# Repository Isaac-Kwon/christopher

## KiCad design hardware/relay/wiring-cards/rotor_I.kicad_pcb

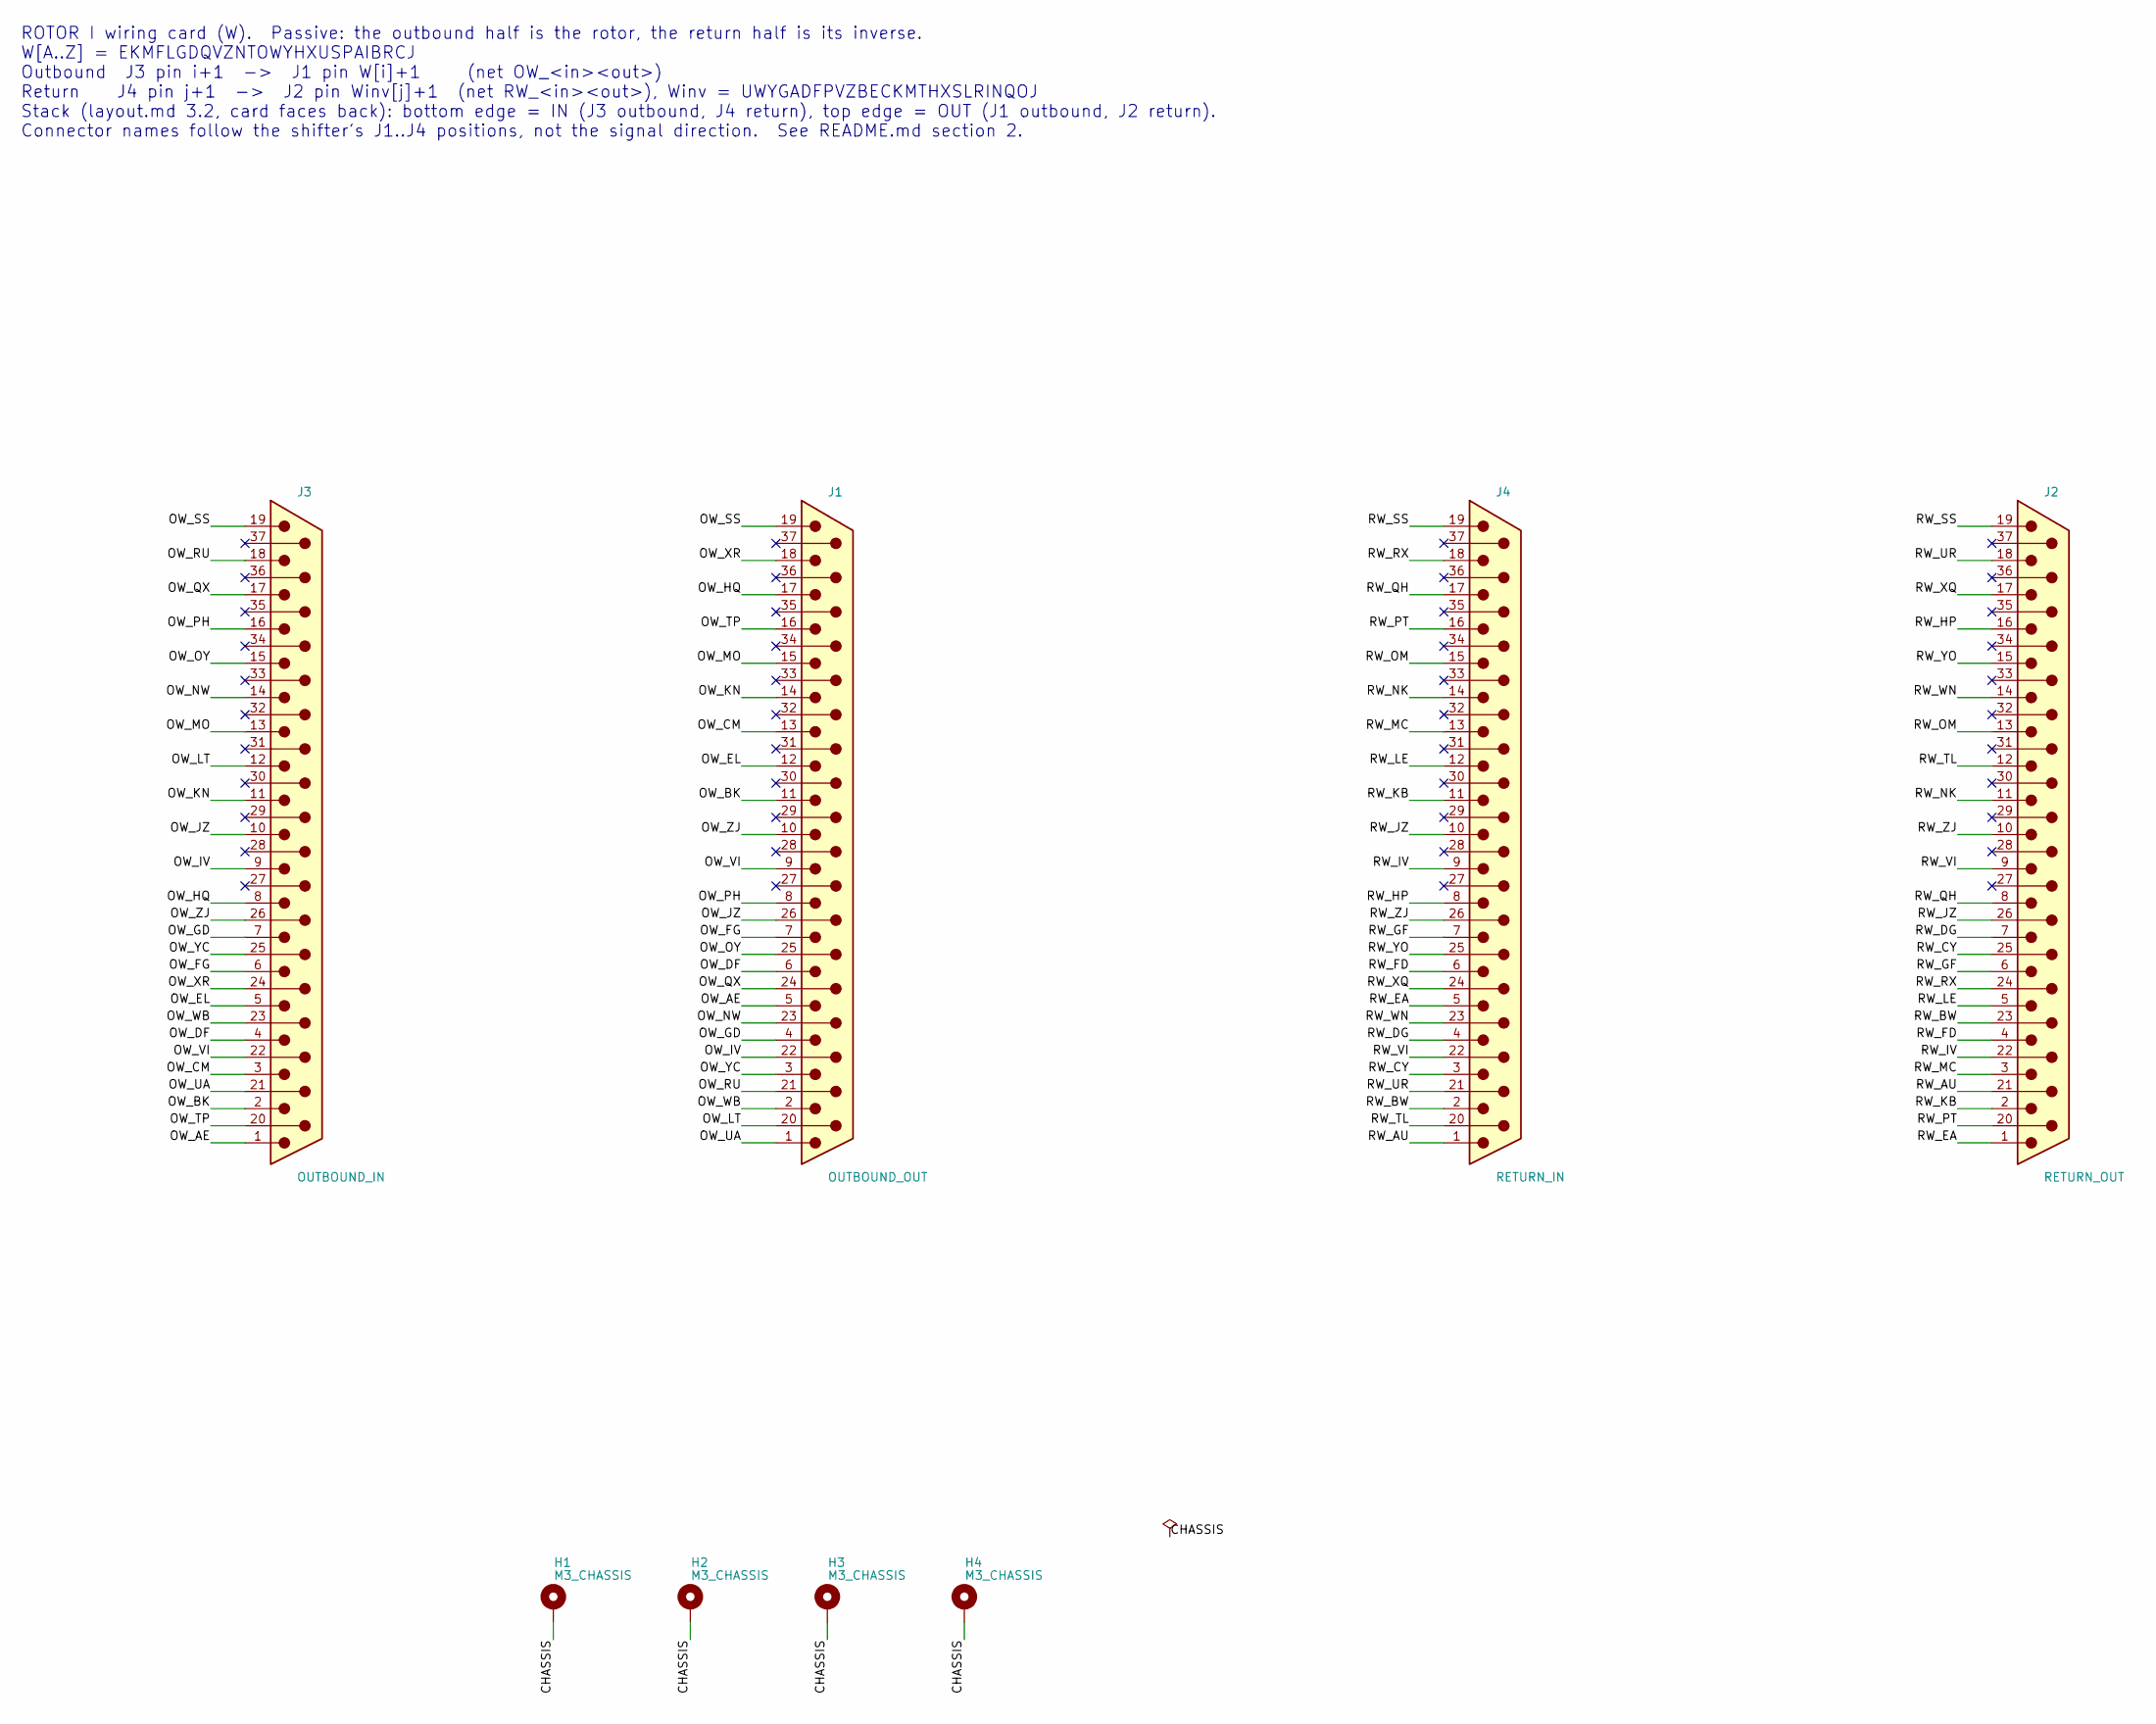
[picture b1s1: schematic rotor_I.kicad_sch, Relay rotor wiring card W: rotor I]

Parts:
H1, H2, H3, H4: M3_CHASSIS; MountingHole_3.2mm_M3_Pad
J1: OUTBOUND_OUT; DSUB-37_Pins_Horizontal_P2.77x2.84mm_EdgePinOffset9.90mm_Ho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
J2: RETURN_OUT; DSUB-37_Pins_Horizontal_P2.77x2.84mm_EdgePinOffset9.90mm_Ho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
J3: OUTBOUND_IN; DSUB-37_Pins_Horizontal_P2.77x2.84mm_EdgePinOffset9.90mm_Ho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
J4: RETURN_IN; DSUB-37_Pins_Horizontal_P2.77x2.84mm_EdgePinOffset9.90mm_Ho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

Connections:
/CHASSIS: H1.1, H2.1, H3.1, H4.1, J1.SH, J2.SH, J3.SH, J4.SH
/OW_AE: J1.5, J3.1
/OW_BK: J1.11, J3.2
/OW_CM: J1.13, J3.3
/OW_DF: J1.6, J3.4
/OW_EL: J1.12, J3.5
/OW_FG: J1.7, J3.6
/OW_GD: J1.4, J3.7
/OW_HQ: J1.17, J3.8
/OW_IV: J1.22, J3.9
/OW_JZ: J1.26, J3.10
/OW_KN: J1.14, J3.11
/OW_LT: J1.20, J3.12
/OW_MO: J1.15, J3.13
/OW_NW: J1.23, J3.14
/OW_OY: J1.25, J3.15
/OW_PH: J1.8, J3.16
/OW_QX: J1.24, J3.17
/OW_RU: J1.21, J3.18
/OW_SS: J1.19, J3.19
/OW_TP: J1.16, J3.20
/OW_UA: J1.1, J3.21
/OW_VI: J1.9, J3.22
/OW_WB: J1.2, J3.23
/OW_XR: J1.18, J3.24
/OW_YC: J1.3, J3.25
/OW_ZJ: J1.10, J3.26
/RW_AU: J2.21, J4.1
/RW_BW: J2.23, J4.2
/RW_CY: J2.25, J4.3
/RW_DG: J2.7, J4.4
/RW_EA: J2.1, J4.5
/RW_FD: J2.4, J4.6
/RW_GF: J2.6, J4.7
/RW_HP: J2.16, J4.8
/RW_IV: J2.22, J4.9
/RW_JZ: J2.26, J4.10
/RW_KB: J2.2, J4.11
/RW_LE: J2.5, J4.12
/RW_MC: J2.3, J4.13
/RW_NK: J2.11, J4.14
/RW_OM: J2.13, J4.15
/RW_PT: J2.20, J4.16
/RW_QH: J2.8, J4.17
/RW_RX: J2.24, J4.18
/RW_SS: J2.19, J4.19
/RW_TL: J2.12, J4.20
/RW_UR: J2.18, J4.21
/RW_VI: J2.9, J4.22
/RW_WN: J2.14, J4.23
/RW_XQ: J2.17, J4.24
/RW_YO: J2.15, J4.25
/RW_ZJ: J2.10, J4.26

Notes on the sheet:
ROTOR I wiring card (W). Passive: the outbound half is the rotor, the return half is its inverse. W[A..Z] = EKMFLGDQVZNTOWYHXUSPAIBRCJ Outbound J3 pin i+1 -> J1 pin W[i]+1 (net OW_<in><out>) Return J4 pin j+1 -> J2 pin Winv[j]+1 (net RW_<in><out>), Winv = UWYGADFPVZBECKMTHXSLRINQOJ Stack (layout.md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

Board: 2 copper layers, 8 parts (0 on the bottom side), 53 nets, no tracks yet.

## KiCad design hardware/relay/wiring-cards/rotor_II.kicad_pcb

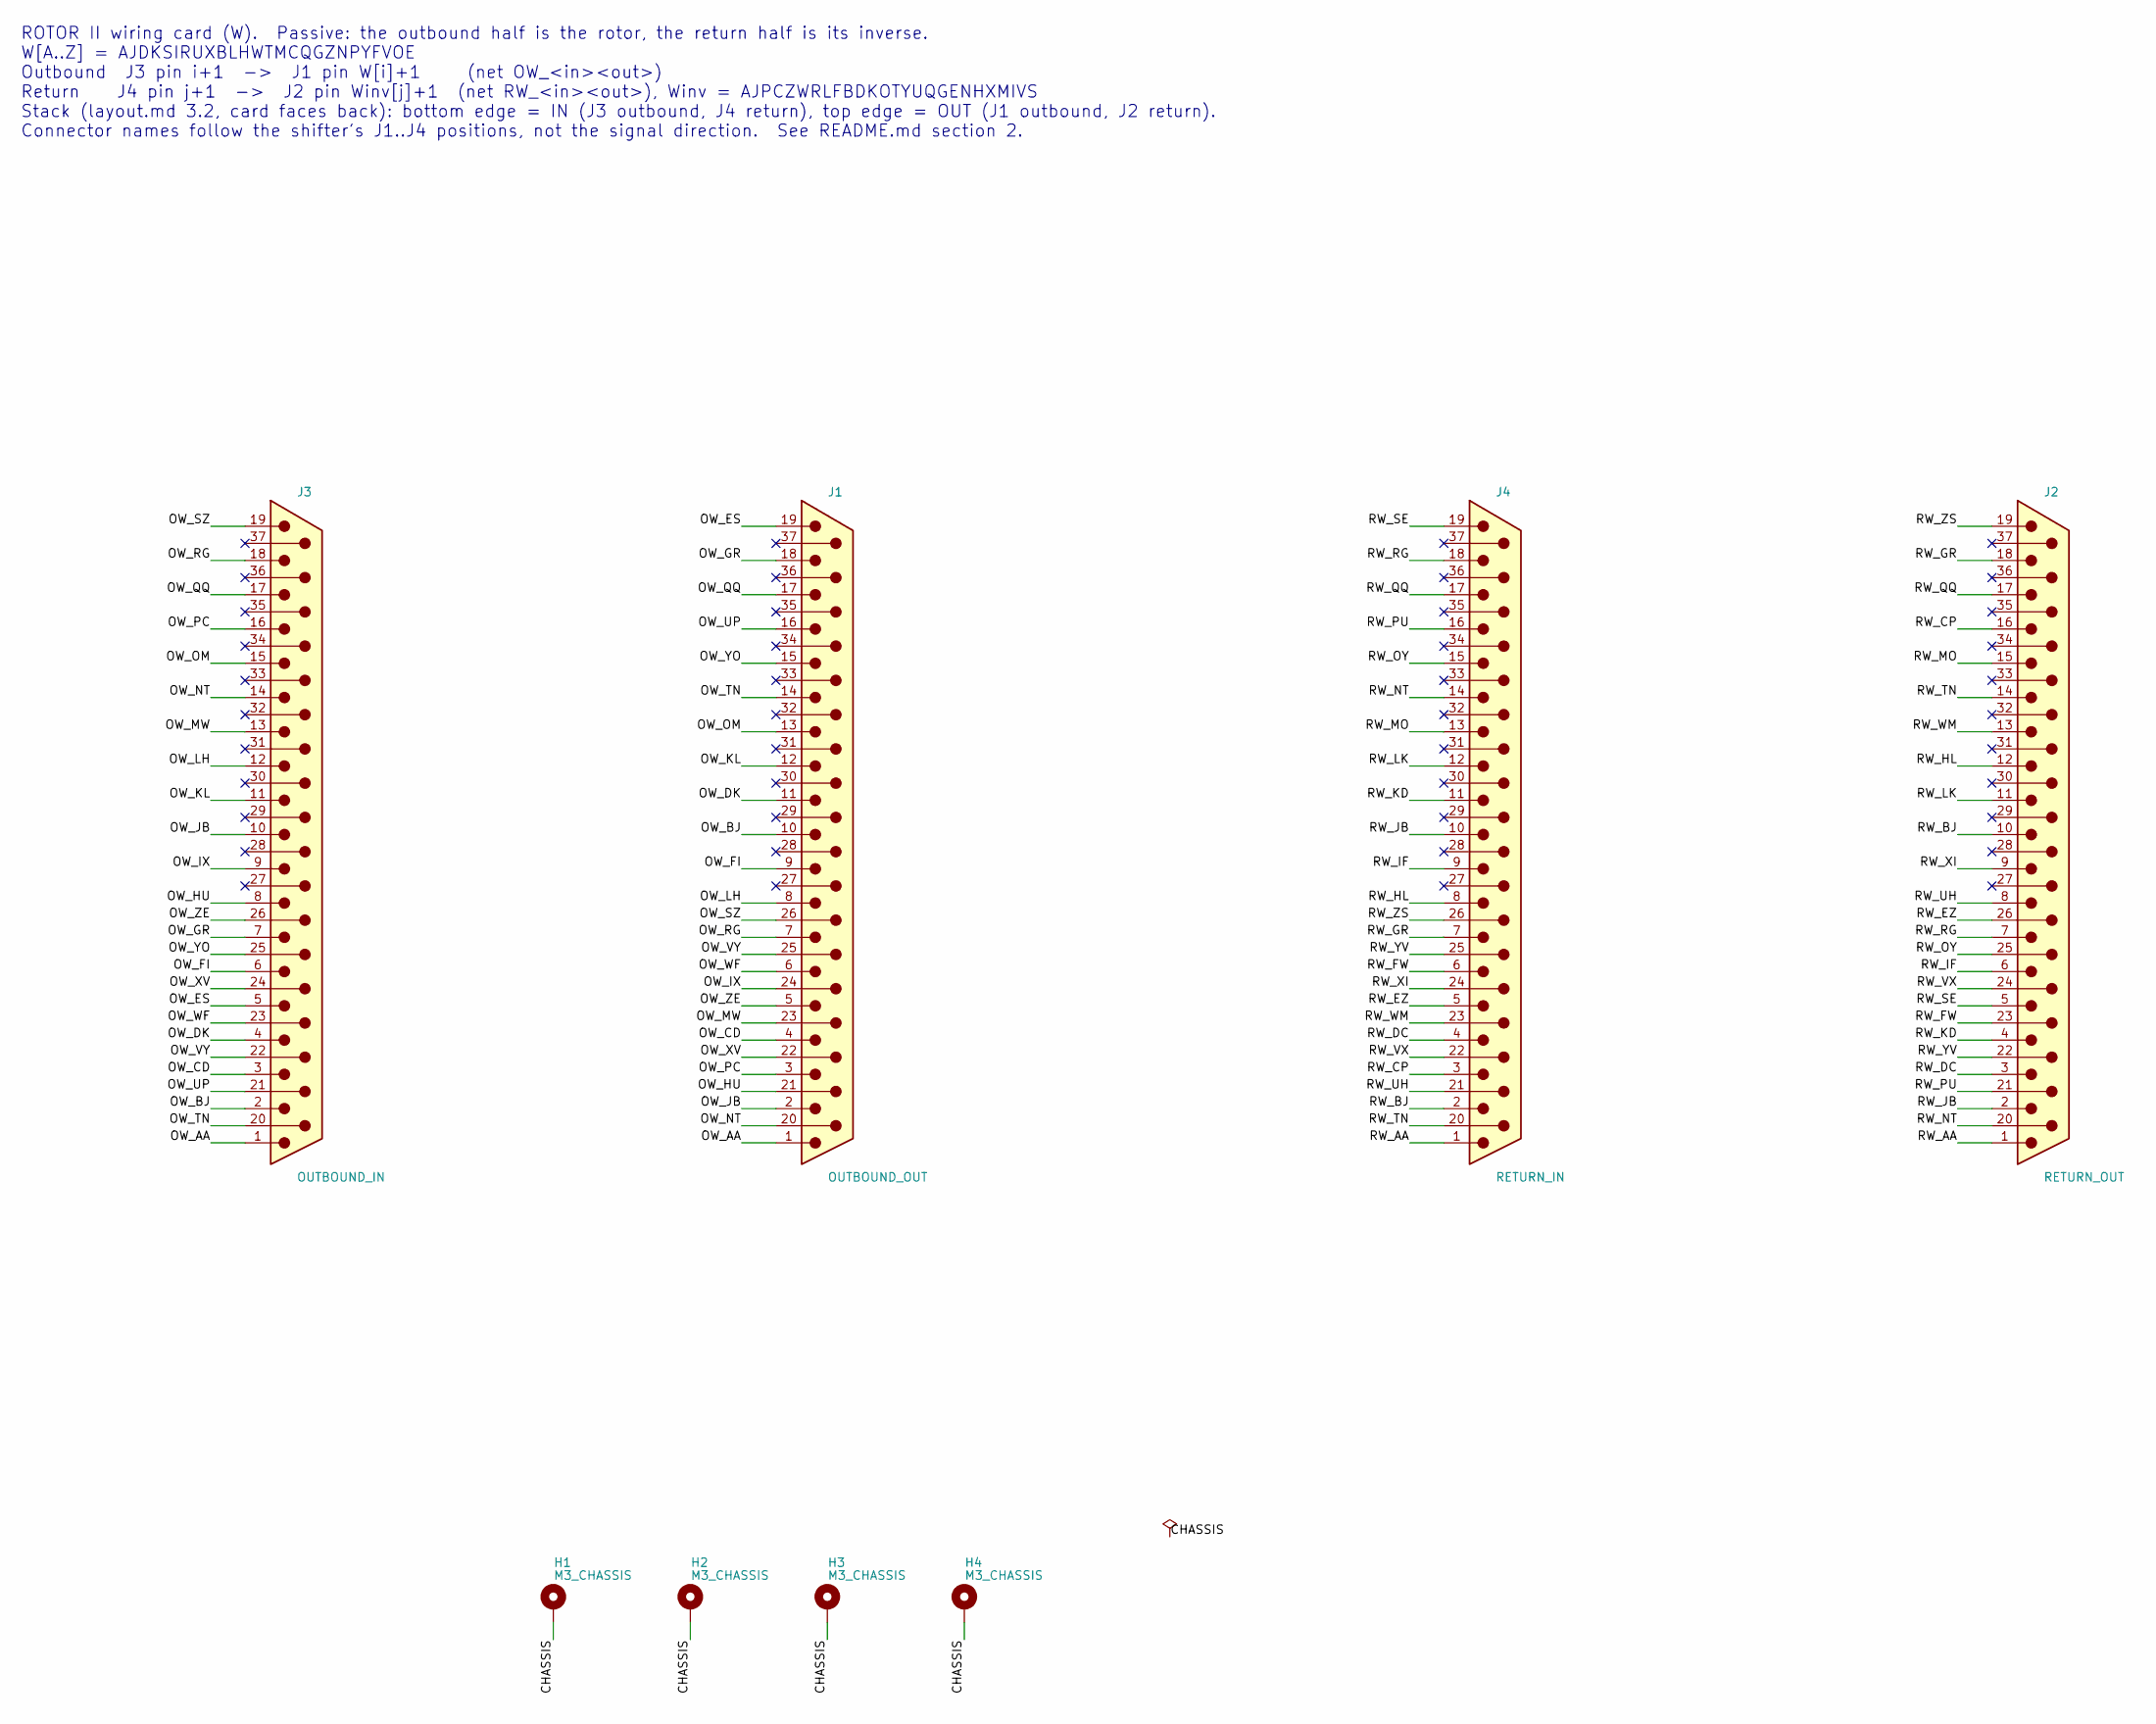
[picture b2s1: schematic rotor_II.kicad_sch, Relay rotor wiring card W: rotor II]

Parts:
H1, H2, H3, H4: M3_CHASSIS; MountingHole_3.2mm_M3_Pad
J1: OUTBOUND_OUT; DSUB-37_Pins_Horizontal_P2.77x2.84mm_EdgePinOffset9.90mm_Ho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
J2: RETURN_OUT; DSUB-37_Pins_Horizontal_P2.77x2.84mm_EdgePinOffset9.90mm_Ho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
J3: OUTBOUND_IN; DSUB-37_Pins_Horizontal_P2.77x2.84mm_EdgePinOffset9.90mm_Ho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
J4: RETURN_IN; DSUB-37_Pins_Horizontal_P2.77x2.84mm_EdgePinOffset9.90mm_Ho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

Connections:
/CHASSIS: H1.1, H2.1, H3.1, H4.1, J1.SH, J2.SH, J3.SH, J4.SH
/OW_AA: J1.1, J3.1
/OW_BJ: J1.10, J3.2
/OW_CD: J1.4, J3.3
/OW_DK: J1.11, J3.4
/OW_ES: J1.19, J3.5
/OW_FI: J1.9, J3.6
/OW_GR: J1.18, J3.7
/OW_HU: J1.21, J3.8
/OW_IX: J1.24, J3.9
/OW_JB: J1.2, J3.10
/OW_KL: J1.12, J3.11
/OW_LH: J1.8, J3.12
/OW_MW: J1.23, J3.13
/OW_NT: J1.20, J3.14
/OW_OM: J1.13, J3.15
/OW_PC: J1.3, J3.16
/OW_QQ: J1.17, J3.17
/OW_RG: J1.7, J3.18
/OW_SZ: J1.26, J3.19
/OW_TN: J1.14, J3.20
/OW_UP: J1.16, J3.21
/OW_VY: J1.25, J3.22
/OW_WF: J1.6, J3.23
/OW_XV: J1.22, J3.24
/OW_YO: J1.15, J3.25
/OW_ZE: J1.5, J3.26
/RW_AA: J2.1, J4.1
/RW_BJ: J2.10, J4.2
/RW_CP: J2.16, J4.3
/RW_DC: J2.3, J4.4
/RW_EZ: J2.26, J4.5
/RW_FW: J2.23, J4.6
/RW_GR: J2.18, J4.7
/RW_HL: J2.12, J4.8
/RW_IF: J2.6, J4.9
/RW_JB: J2.2, J4.10
/RW_KD: J2.4, J4.11
/RW_LK: J2.11, J4.12
/RW_MO: J2.15, J4.13
/RW_NT: J2.20, J4.14
/RW_OY: J2.25, J4.15
/RW_PU: J2.21, J4.16
/RW_QQ: J2.17, J4.17
/RW_RG: J2.7, J4.18
/RW_SE: J2.5, J4.19
/RW_TN: J2.14, J4.20
/RW_UH: J2.8, J4.21
/RW_VX: J2.24, J4.22
/RW_WM: J2.13, J4.23
/RW_XI: J2.9, J4.24
/RW_YV: J2.22, J4.25
/RW_ZS: J2.19, J4.26

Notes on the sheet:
ROTOR II wiring card (W). Passive: the outbound half is the rotor, the return half is its inverse. W[A..Z] = AJDKSIRUXBLHWTMCQGZNPYFVOE Outbound J3 pin i+1 -> J1 pin W[i]+1 (net OW_<in><out>) Return J4 pin j+1 -> J2 pin Winv[j]+1 (net RW_<in><out>), Winv = AJPCZWRLFBDKOTYUQGENHXMIVS Stack (layout.m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

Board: 2 copper layers, 8 parts (0 on the bottom side), 53 nets, no tracks yet.

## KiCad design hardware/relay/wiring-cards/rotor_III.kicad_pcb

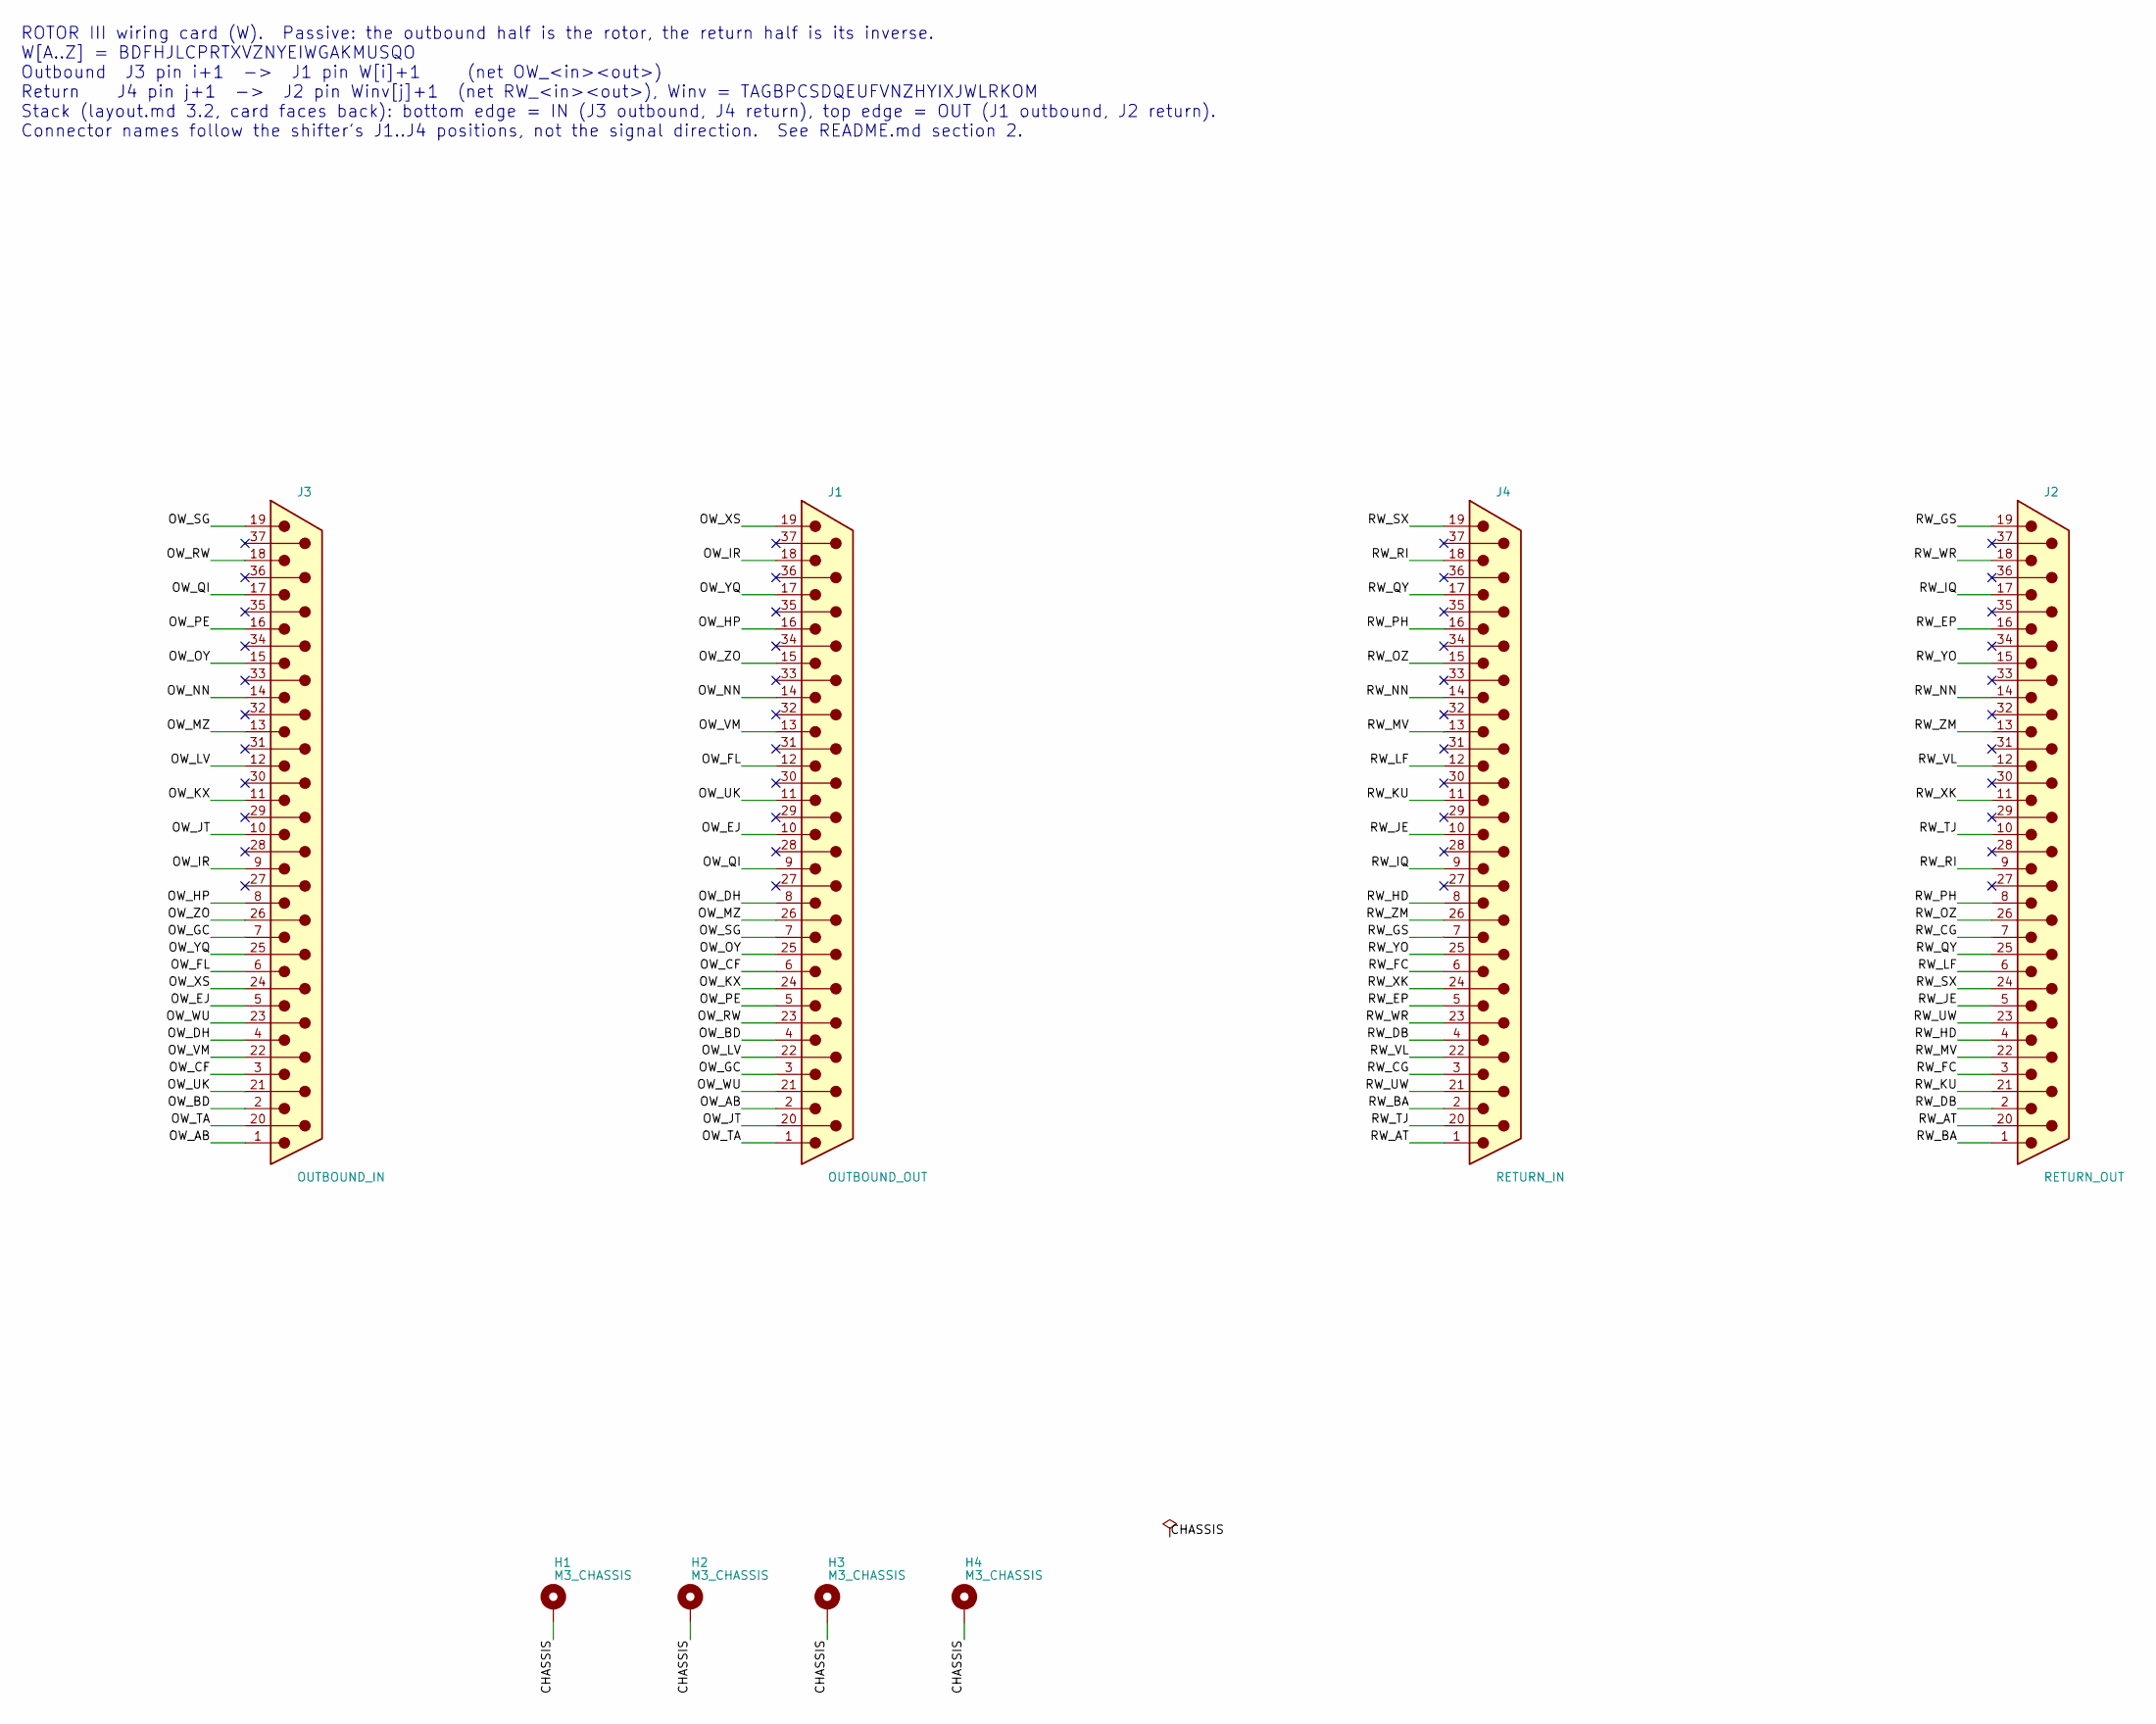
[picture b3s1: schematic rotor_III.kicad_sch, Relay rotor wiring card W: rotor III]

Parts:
H1, H2, H3, H4: M3_CHASSIS; MountingHole_3.2mm_M3_Pad
J1: OUTBOUND_OUT; DSUB-37_Pins_Horizontal_P2.77x2.84mm_EdgePinOffset9.90mm_Ho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
J2: RETURN_OUT; DSUB-37_Pins_Horizontal_P2.77x2.84mm_EdgePinOffset9.90mm_Ho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
J3: OUTBOUND_IN; DSUB-37_Pins_Horizontal_P2.77x2.84mm_EdgePinOffset9.90mm_Ho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
J4: RETURN_IN; DSUB-37_Pins_Horizontal_P2.77x2.84mm_EdgePinOffset9.90mm_Ho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

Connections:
/CHASSIS: H1.1, H2.1, H3.1, H4.1, J1.SH, J2.SH, J3.SH, J4.SH
/OW_AB: J1.2, J3.1
/OW_BD: J1.4, J3.2
/OW_CF: J1.6, J3.3
/OW_DH: J1.8, J3.4
/OW_EJ: J1.10, J3.5
/OW_FL: J1.12, J3.6
/OW_GC: J1.3, J3.7
/OW_HP: J1.16, J3.8
/OW_IR: J1.18, J3.9
/OW_JT: J1.20, J3.10
/OW_KX: J1.24, J3.11
/OW_LV: J1.22, J3.12
/OW_MZ: J1.26, J3.13
/OW_NN: J1.14, J3.14
/OW_OY: J1.25, J3.15
/OW_PE: J1.5, J3.16
/OW_QI: J1.9, J3.17
/OW_RW: J1.23, J3.18
/OW_SG: J1.7, J3.19
/OW_TA: J1.1, J3.20
/OW_UK: J1.11, J3.21
/OW_VM: J1.13, J3.22
/OW_WU: J1.21, J3.23
/OW_XS: J1.19, J3.24
/OW_YQ: J1.17, J3.25
/OW_ZO: J1.15, J3.26
/RW_AT: J2.20, J4.1
/RW_BA: J2.1, J4.2
/RW_CG: J2.7, J4.3
/RW_DB: J2.2, J4.4
/RW_EP: J2.16, J4.5
/RW_FC: J2.3, J4.6
/RW_GS: J2.19, J4.7
/RW_HD: J2.4, J4.8
/RW_IQ: J2.17, J4.9
/RW_JE: J2.5, J4.10
/RW_KU: J2.21, J4.11
/RW_LF: J2.6, J4.12
/RW_MV: J2.22, J4.13
/RW_NN: J2.14, J4.14
/RW_OZ: J2.26, J4.15
/RW_PH: J2.8, J4.16
/RW_QY: J2.25, J4.17
/RW_RI: J2.9, J4.18
/RW_SX: J2.24, J4.19
/RW_TJ: J2.10, J4.20
/RW_UW: J2.23, J4.21
/RW_VL: J2.12, J4.22
/RW_WR: J2.18, J4.23
/RW_XK: J2.11, J4.24
/RW_YO: J2.15, J4.25
/RW_ZM: J2.13, J4.26

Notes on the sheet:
ROTOR III wiring card (W). Passive: the outbound half is the rotor, the return half is its inverse. W[A..Z] = BDFHJLCPRTXVZNYEIWGAKMUSQO Outbound J3 pin i+1 -> J1 pin W[i]+1 (net OW_<in><out>) Return J4 pin j+1 -> J2 pin Winv[j]+1 (net RW_<in><out>), Winv = TAGBPCSDQEUFVNZHYIXJWLRKOM Stack (layout.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

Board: 2 copper layers, 8 parts (0 on the bottom side), 53 nets, no tracks yet.

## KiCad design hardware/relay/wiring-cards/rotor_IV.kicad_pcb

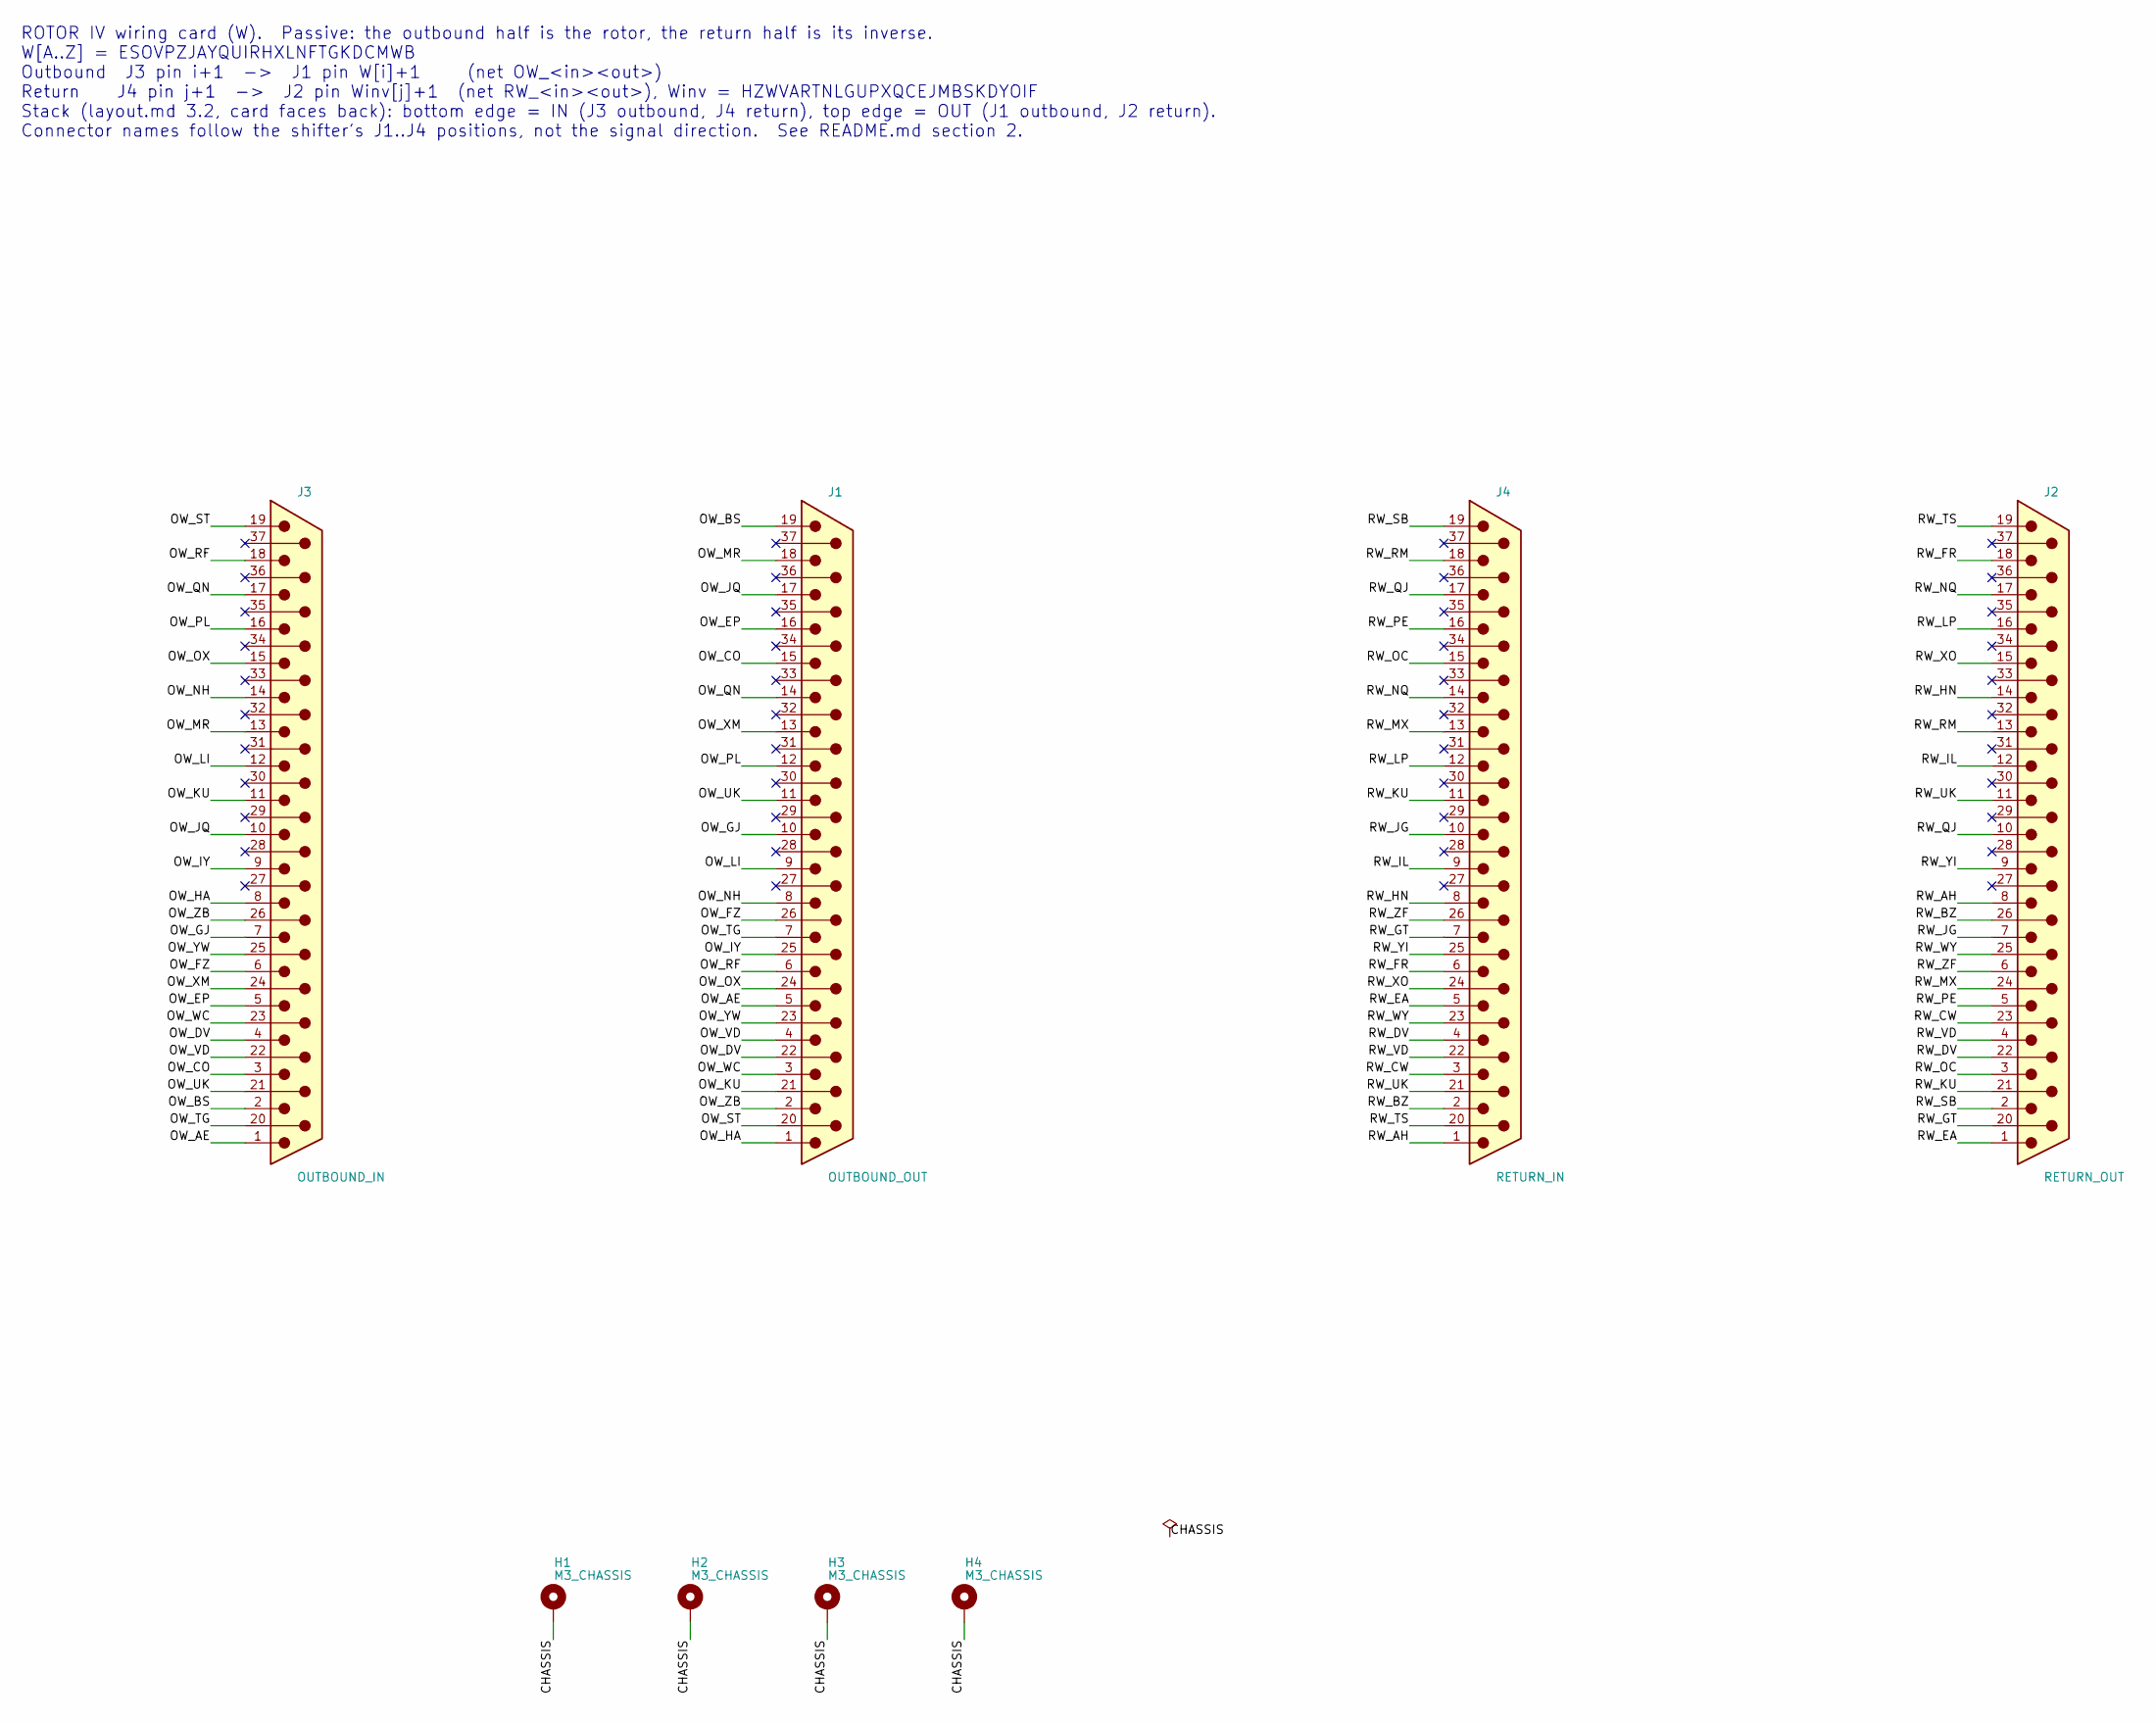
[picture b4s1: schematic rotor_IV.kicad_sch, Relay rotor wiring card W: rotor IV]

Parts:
H1, H2, H3, H4: M3_CHASSIS; MountingHole_3.2mm_M3_Pad
J1: OUTBOUND_OUT; DSUB-37_Pins_Horizontal_P2.77x2.84mm_EdgePinOffset9.90mm_Ho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
J2: RETURN_OUT; DSUB-37_Pins_Horizontal_P2.77x2.84mm_EdgePinOffset9.90mm_Ho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
J3: OUTBOUND_IN; DSUB-37_Pins_Horizontal_P2.77x2.84mm_EdgePinOffset9.90mm_Ho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
J4: RETURN_IN; DSUB-37_Pins_Horizontal_P2.77x2.84mm_EdgePinOffset9.90mm_Ho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

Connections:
/CHASSIS: H1.1, H2.1, H3.1, H4.1, J1.SH, J2.SH, J3.SH, J4.SH
/OW_AE: J1.5, J3.1
/OW_BS: J1.19, J3.2
/OW_CO: J1.15, J3.3
/OW_DV: J1.22, J3.4
/OW_EP: J1.16, J3.5
/OW_FZ: J1.26, J3.6
/OW_GJ: J1.10, J3.7
/OW_HA: J1.1, J3.8
/OW_IY: J1.25, J3.9
/OW_JQ: J1.17, J3.10
/OW_KU: J1.21, J3.11
/OW_LI: J1.9, J3.12
/OW_MR: J1.18, J3.13
/OW_NH: J1.8, J3.14
/OW_OX: J1.24, J3.15
/OW_PL: J1.12, J3.16
/OW_QN: J1.14, J3.17
/OW_RF: J1.6, J3.18
/OW_ST: J1.20, J3.19
/OW_TG: J1.7, J3.20
/OW_UK: J1.11, J3.21
/OW_VD: J1.4, J3.22
/OW_WC: J1.3, J3.23
/OW_XM: J1.13, J3.24
/OW_YW: J1.23, J3.25
/OW_ZB: J1.2, J3.26
/RW_AH: J2.8, J4.1
/RW_BZ: J2.26, J4.2
/RW_CW: J2.23, J4.3
/RW_DV: J2.22, J4.4
/RW_EA: J2.1, J4.5
/RW_FR: J2.18, J4.6
/RW_GT: J2.20, J4.7
/RW_HN: J2.14, J4.8
/RW_IL: J2.12, J4.9
/RW_JG: J2.7, J4.10
/RW_KU: J2.21, J4.11
/RW_LP: J2.16, J4.12
/RW_MX: J2.24, J4.13
/RW_NQ: J2.17, J4.14
/RW_OC: J2.3, J4.15
/RW_PE: J2.5, J4.16
/RW_QJ: J2.10, J4.17
/RW_RM: J2.13, J4.18
/RW_SB: J2.2, J4.19
/RW_TS: J2.19, J4.20
/RW_UK: J2.11, J4.21
/RW_VD: J2.4, J4.22
/RW_WY: J2.25, J4.23
/RW_XO: J2.15, J4.24
/RW_YI: J2.9, J4.25
/RW_ZF: J2.6, J4.26

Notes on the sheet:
ROTOR IV wiring card (W). Passive: the outbound half is the rotor, the return half is its inverse. W[A..Z] = ESOVPZJAYQUIRHXLNFTGKDCMWB Outbound J3 pin i+1 -> J1 pin W[i]+1 (net OW_<in><out>) Return J4 pin j+1 -> J2 pin Winv[j]+1 (net RW_<in><out>), Winv = HZWVARTNLGUPXQCEJMBSKDYOIF Stack (layout.m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

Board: 2 copper layers, 8 parts (0 on the bottom side), 53 nets, no tracks yet.
